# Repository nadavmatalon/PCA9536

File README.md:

# PCA9536 DRIVER

&nbsp;&nbsp;&nbsp;&nbsp;&nbsp;&nbsp;&nbsp;&nbsp;&nbsp;&nbsp;

&nbsp;&nbsp;&nbsp;&nbsp;&nbsp;&nbsp;&nbsp;&nbsp;&nbsp;&nbsp;

&nbsp;&nbsp;&nbsp;&nbsp;&nbsp;&nbsp;&nbsp;&nbsp;&nbsp;&nbsp;

## INTRODUCTION

The PCA9536 is a 4-Channel GPIO Expander with a hardware I2C interface.

The device's 4 channels (i.e. I/O pins) may be controlled all at the same time or individually in terms of their:  
\[1\] Mode (INPUT / OUTPUT), \[2\] State (for output pin mode only: HIGH / LOW), and \[3\] Polarity (for input pin mode only: NON-INVERTED INPUT / INVERTED INPUT). The State (LOW / HIGH) of pins in input mode may be read, whereas thoat of pins in output mode may be either read or written to.

This library contains a complete driver for the PCA9536 exposing all the above functionality, as well as allowing uses to toggle the state of pins in input mode, and the option to recieve verbose information re the device's current settings and/or I2C communication results.

Source: [PCA9536 DATASHEET](http://www.nxp.com/documents/data_sheet/PCA9536.pdf)

## REPOSITORY CONTENTS

- **PCA9536.h** - Library Header file.
- **PCA9536.cpp** - Library Compilation.
- **/utility** 
  - **PCA9536InfoStr.h** - Header file containing a functional extention of the library to include generating pritable information String (see Note #5 below).
  - **PCA9536ComStr.h** - Header file containing a functional extention of the library to include generating a pritable I2C Communication Result String (see Note #6 below).
  - **PCA9536_PString.h** - Header file for PString class (lighter alternative to String class) 
  - **PCA9536_PString.cpp** - Compilation file for PString class (lighter alternative to String class) 
- **/examples**  
  - **/PCA9536_Test**
    - **PCA9536_Test.ino** - A basic sketch for testing whether the PCA9536 is hooked-up and operating correctly.
  - **/PCA9536_Usage**
    - **PCA9536_Usage.ino** - A much more extensive sketch offering a complete usage illustration, as well as a rubust testing mechanism.
  - **/PCA9536_Info**
    - **PCA9536_Info.ino** - A short sketch showing how to generate a Printable Device Information String of the PCA9536's current settings (i.e. Configuration, Limit &anp; Hysteresis registers, etc.).
  - **/PCA9536_I2C_Status**
    - **PCA9536_I2C_Status.ino** - A short sketch for verifying I2C communication has been established between the controller and the PCA9536.
- **/extras** 
  - **License.txt** - A cope of the end-user license agreement.  
  - **/eagle**
    - **PCA9536.sch** - Schematic file for the PCA9536 breakout board.
    - **PCA9536.brd** - Board layout file for the PCA9536 breakout board.
  - **/images**
    - **pca9536_pinout.png** - Pinout image of the PCA9536.
- **keywords.txt** - Keywords for this library which will be highlighted in sketches within the Arduino IDE. 
- **library.properties** - General library properties for the Arduino's IDE (>1.5) Library Package Manager.
- **README.md** - The readme file for this library.
- **library.json** - JSON file for the Arduino's IDE (>1.5) Package Manager.

## HOOK-UP

PIN 1 (IO0) - connect to device requiring digital I/O pin (or leave unconnected)  
PIN 2 (IO1) - connect to device requiring digital I/O pin (or leave unconnected)  
PIN 3 (IO2) - connect to device requiring digital I/O pin (or leave unconnected)  
PIN 4 (GND) - Connect to Arduino GND  
PIN 5 (IO3) - connect to device requiring digital I/O pin (or leave unconnected)  
PIN 6 (SCL) - Connect to Arduino Pin A5 with a 2K2 (400MHz) or 10K (100MHz) pull-up resistor  
PIN 7 (SDA) - Connect to Arduino Pin A4 with a 2K2 (400MHz) or 10K (100MHz) pull-up resistor  
PIN 8 (VCC) - Connect to Arduino 5V output  
DECOUPING   - Connect a 0.1uF Ceramic Capacitor between the PCA9536's VCC & GND pins  

## GENERAL NOTES

1) __I2C Communications Library Dependency__

This library depends on the Arduino IDE's native '[Wire](https://github.com/arduino/Arduino/tree/master/hardware/arduino/avr/libraries/Wire)' library for I2C communication between the Arduino (Master) and the PCA9536 (Slave). 

2) __INPUT &amp; OUTPUT REGISTER VALUES__

It is important to note that the PCA9536 uses an inverse value scheme for designating INPUT and OUTPUT modes than that of the Arduino. In the Arduino environment, INPUT is designated by 0 and OUTPUT by 1, whereas the PCA9536 has INPUT as 1 and OUTPUT as 0.

3) __PULL-UP RESISTORS__

All 4 channels of the PCA9536 have weak pull-up resistors attached (~100K). Hence, if a pin is left 'floating' (or unconnected), it will default to a HIGH state.

4) __Constructor &amp; Destructor__

As PCA9536 instances are initialized without parameters (recall that the single I2C address of the device is factory hardwired), the constructor and destructor have a slightly unconventional format in that they do not include the usual parentheses at the end. For concrete illustrations, see the example sketches bundled in this library.

5) __Device Information String__

It is possible to extend the PCA9536 Library to include a function for generating a pritable device information string showing all the relevant details about the devices current settings. As the additional functionality comes at the cost of increased memory footprint, it was implemented as an optional add-on rather than added directly to the core PCA9536 Library. See the [PCA9536_Info](https://github.com/nadavmatalon/PCA9536/blob/master/examples/PCA9536_Info/PCA9536_Info.ino) example sketch for detailed explanation and an actual usage demo.

6) __Device I2C Communications String__

It is also possible to extend the PCA9536 Library to include a function for generating a pritable I2C Communications string showing the result of each I2C transaction in a human-friendly way, something that may be useful, for example, during debugging sessions. As the additional functionality comes at the cost of increased memory footprint, it was implemented as an optional add-on rather than added directly to the core PCA9536 Library. See the [PCA9536_I2C_Status](https://github.com/nadavmatalon/PCA9536/blob/master/examples/PCA9536_I2C_Status/PCA9536_I2C_Status.ino) example sketch for detailed explanation and an actual usage demo.

## I2C ADDRESS

The PCA9536 has a single I2C address (factory hardwired):

| PART NO.  | BIN      | HEX  | DEC | MARKING |
|-----------|----------|------|-----|---------|
| PCA9536D  | 01000001 | 0x41 | 65  | PCA9536 |

## LIBRARY INSTALLATION & SETUP

Begin by installing the library either by using the Arduino IDE's Installation Wizard (Arduino Version >1.5) or simply by directly downloading the library's ZIP folder  from Github, extracting it, and copying the extraxcted folder into your Arduino '/libraries' folder (don't forget to re-start the Arduino IDE after coping the folder so that the new library will show up in the list of installed libraries).

Next, include the library at the top of the sketch as follows:

```
#include "PCA9536.h"
```

At this point you can construct a new PCA9536 instance(s) by using the following command (place at the top of the sketch after the 'include' line):

```
PCA9536 device_name;  // Notice that the constructor doesn't use parenthesis after device_name! (see Note #3 above)
```

>Replace '__device_name__' above with a name of your choice. As the PCA9536 comes with a single hardwired I2C address, initializations of the class instance is done automatically to that address.

Next, make sure to inlude an instruction for initializing the I2C Bus for the [Wire Library](https://github.com/arduino/Arduino/tree/master/hardware/arduino/avr/libraries/Wire), as follows:

(There's no need to include the Wire Library at the top of the sketch as it's already included by the PCA9536 Library)

```
void setup() {
    Wire.begin();
    // ...other setup code...
}
```

## LIBRARY FUNCTIONS

With the library installed & included in the sketch, and an PCA9536 instance created, the following functions are available (see the usage example sketch for a detailed implementation):

__Note About Methods' Return Values:__  
All 'get' methods return some sort of value (e.g. temp reading, hysteresis setting, etc.), while all 'set' methods return nothing. Nevertheless, ALL methods implicitly update the library's __I2C _comBuffer__ (=communication buffer) after each I2C transmission. The reason for this functional design is to maintain structural coherance between the 'get' and 'set' methods. As 'get' methods cannot return both the desired value and the I2C transmission's result simultaniously. Consequently, if the relevant value hasn't been obtained by a particular 'get' method, the user can simply check the content of the _comBuffer to see what error occured. Similarly, it is possible to check if a particular setting has been successfully applied via a 'set' method either by preforming the corresponding 'get' method - e.g. getHystC() after using setHystC() - or by checking the content of the _comBuffer (0 indicates a successful transmission, 1-6 indicate an error as listed below). 

__ping();__                                  
Parameters:&nbsp;&nbsp;&nbsp;None  
Description:&nbsp;&nbsp;&nbsp;Searches for the PCA9536 at the pre-defined I2C Bus address &amp; returns byte with the relevant success/error code, as follows:  
0  ... Success (no error)  
1  ... Buffer overflow  
2  ... Address sent, NACK received  
3  ... Data send, NACK received  
4  ... Other error (lost bus arbitration, bus error, etc.)  
5  ... Timed-out while trying to become Bus Master  
6  ... Timed-out while waiting for data to be sent  
\>6 ... Unlisted error (potential future implementation/s)<br>

Returns:&nbsp;&nbsp;&nbsp;&nbsp;&nbsp;&nbsp;&nbsp;&nbsp;&nbsp;byte  

__getMode();__  
Parameters:&nbsp;&nbsp;&nbsp;IO0 / IO1 / IO2 / IO3  
Description:&nbsp;&nbsp;Gets the selected pin's current mode (1 = INPUT [default]/ 0 = OUTPUT) (For more info, see General Note #1 above).  
Returns:&nbsp;&nbsp;&nbsp;&nbsp;&nbsp;&nbsp;&nbsp;&nbsp;byte  

__getState();__  
Parameters:&nbsp;&nbsp;&nbsp;IO0 / IO1 / IO2 / IO3  
Description:&nbsp;&nbsp;Gets the selected pin's current state (0 = LOW / 1 = HIGH [default]).  
Returns:&nbsp;&nbsp;&nbsp;&nbsp;&nbsp;&nbsp;&nbsp;&nbsp;byte  

__getPolarity();__  
Parameters:&nbsp;&nbsp;&nbsp;IO0 / IO1 / IO2 / IO3  
Description:&nbsp;&nbsp;Gets the selected INPUT pin's current polarity (0 = NON-INVERTED [default] / 1 = INVERTED). Note that this is relevant only for INPUT pins. The polarity setting determinwes whether reading an INPUT pin returns its actual state or an inverted state.  
Returns:&nbsp;&nbsp;&nbsp;&nbsp;&nbsp;&nbsp;&nbsp;&nbsp;byte  

__setMode();__  
Parameters:&nbsp;&nbsp;&nbsp;To set a single pin: IO0 / IO1 / IO2 / IO3, IO_INPUT [default] / IO_OUTPUT | To set all pins at once: IO_INPUT [default] / IO_OUTPUT  
Description:&nbsp;&nbsp;Sets the selected pin/s mode (INPUT / OUTPUT).  
Returns:&nbsp;&nbsp;&nbsp;&nbsp;&nbsp;&nbsp;&nbsp;&nbsp;None

__setState();__  
Parameters:&nbsp;&nbsp;&nbsp;To set a single OUTPUT pin: IO0 / IO1 / IO2 / IO3, IO_LOW / IO_HIGH [default] | To set all OUTPUT pins at once: IO_LOW / IO_HIGH [default]
Description:&nbsp;&nbsp;Sets the selected pin/s state (LOW / HIGH). Note that this is relevant only for OUTPUT pins.   
Returns:&nbsp;&nbsp;&nbsp;&nbsp;&nbsp;&nbsp;&nbsp;&nbsp;None

__toggleState();__  
Parameters:&nbsp;&nbsp;&nbsp;To toggle the state of a single OUTPUT pin: IO0 / IO1 / IO2 / IO3 | To toggle all OUTPUT pins at once: None
Description:&nbsp;&nbsp;Toggles the selected pin/s state (LOW / HIGH). Note that this is relevant only for OUTPUT pins.   
Returns:&nbsp;&nbsp;&nbsp;&nbsp;&nbsp;&nbsp;&nbsp;&nbsp;None

__setPolarity();__  
Parameters:&nbsp;&nbsp;&nbsp;To set a single INPUT pin: IO0 / IO1 / IO2 / IO3, IO_NON_INVERTED [default] / IO_INVERTED | To set all INPUT pins at once: IO_NON_INVERTED [default] / IO_INVERTED  
Description:&nbsp;&nbsp;Sets the selected pin/s polarity (NON-INVERTED / INVERTED). Note that this is relevant only for INPUT pins.  
Returns:&nbsp;&nbsp;&nbsp;&nbsp;&nbsp;&nbsp;&nbsp;&nbsp;None  

__reset();__  
Parameters:&nbsp;&nbsp;&nbsp;None  
Description:&nbsp;&nbsp;&nbsp;Resets all 4 channels of the PCA9536 to their power-up default settings, as follows:  

* MODE: INPUT
* STATE: HIGH
* POLARITY: NON-INVERTED
* REGISTRY POINTER: INPUT

Returns:&nbsp;&nbsp;&nbsp;&nbsp;&nbsp;&nbsp;&nbsp;&nbsp;&nbsp;None  

__getComResult();__  
Parameters:&nbsp;&nbsp;&nbsp;None  
Description:&nbsp;&nbsp;Returns the latest I2C Communication result code (see Success/Error codes above)  
Returns:&nbsp;&nbsp;&nbsp;&nbsp;&nbsp;&nbsp;&nbsp;&nbsp;byte  

__Destructor__  
If you want to destruct an instantiated PCA9536 object, you can use the following method to do so:  

```
~PCA9536 device_name;      // Notice that the deconstructor doesn't use parenthesis after device_name! (see Note #3 above)
```
>__NOTE__: replace the '__device_name__' above with the name of your PCA9536 device.

## Extended Functionality*

(* requires an additional '\#include' of the relevant *.h file as shown in the corresponding example sketches)

__PCA9536ComStr();__  
Parameters:&nbsp;&nbsp;&nbsp;Name of an initialized PCA9536 instance  
Description:&nbsp;&nbsp;Returns printable string containing human-friendly information about the device's latest I2C communication result  
Returns:&nbsp;&nbsp;&nbsp;&nbsp;&nbsp;&nbsp;&nbsp;&nbsp;PString

__PCA9536InfoStr();__  
Parameters:&nbsp;&nbsp;&nbsp;Name of an initialized PCA9536 instance  
Description:&nbsp;&nbsp;Returns printable string containing detailed information about the device's current settings   
Returns:&nbsp;&nbsp;&nbsp;&nbsp;&nbsp;&nbsp;&nbsp;&nbsp;PString

## RUNNING THE EXAMPLE SKETCHES

1) Start the Arduino IDE and open the relevant example sketch  
2) Hook-up the PCA9536 to the Arduino as explained in the sketch's notes  
3) Upload the sketch to the Arduino  
4) Open the Serial Communications Window (make sure the baud-rate is set to 9600 or change it in the sketch to match your Serial Port's buad-rate)  

## BUG REPORTS

Please report any issues/bugs/suggestions at the [Issues](https://github.com/nadavmatalon/PCA9536/issues) section of this Github repository.

## TODO

## VERSION HISTORY

__Ver. 1.0.0__ - First release (24.10.16)  

## LICENSE

[The MIT License (MIT)](https://opensource.org/licenses/MIT)
Copyright (c) 2016 Nadav Matalon

Permission is hereby granted, free of charge, to any person obtaining a copy of this software and associated documentation files (the "Software"), to deal in the Software without restriction, including without limitation the rights to use, copy, modify, merge, publish, distribute, sublicense, and/or sell copies of the Software, and to permit persons to whom the Software is furnished to do so, subject to the following conditions:

The above copyright notice and this permission notice shall be included in all copies or substantial portions of the Software.

THE SOFTWARE IS PROVIDED "AS IS", WITHOUT WARRANTY OF ANY KIND, EXPRESS OR IMPLIED, INCLUDING BUT NOT LIMITED TO THE WARRANTIES OF MERCHANTABILITY, FITNESS FOR A PARTICULAR PURPOSE AND NONINFRINGEMENT. IN NO EVENT SHALL THE AUTHORS OR COPYRIGHT HOLDERS BE LIABLE FOR ANY CLAIM, DAMAGES OR OTHER LIABILITY, WHETHER IN AN ACTION OF CONTRACT, TORT OR OTHERWISE, ARISING FROM, OUT OF OR IN CONNECTION WITH THE SOFTWARE OR THE USE OR OTHER DEALINGS IN THE SOFTWARE.

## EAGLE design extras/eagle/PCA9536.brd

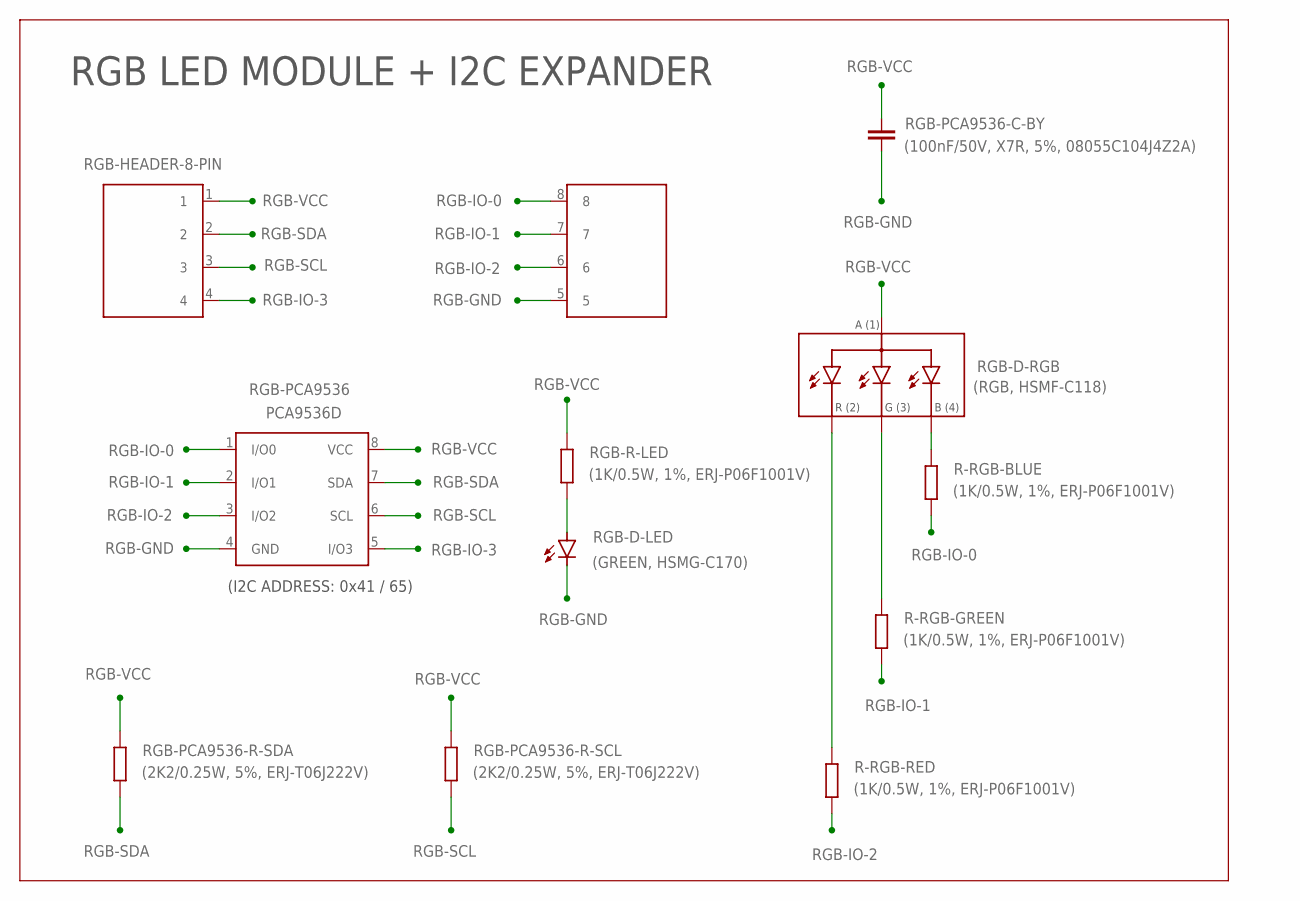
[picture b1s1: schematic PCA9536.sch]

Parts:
R-RGB-BLUE: (1K/0.5W, 1%, ERJ-P06F1001V); 0805
R-RGB-GREEN: (1K/0.5W, 1%, ERJ-P06F1001V); 0805
R-RGB-RED: (1K/0.5W, 1%, ERJ-P06F1001V); 0805
RGB-D-LED: (GREEN, HSMG-C170); DIODE_0805
RGB-D-RGB: (RGB, HSMF-C118); DIODE_LED_1210_RGB
RGB-J1: RGB-HEADER-8-PIN; HEADER_2.54MM_8_PIN_VER
RGB-PCA9536: PCA9536D; SOIC-8-NARROW
RGB-PCA9536-C-BY: (100nF/50V, X7R, 5%, 08055C104J4Z2A); 0805
RGB-PCA9536-R-SCL, RGB-PCA9536-R-SDA: (2K2/0.25W, 5%, ERJ-T06J222V); 0805
RGB-R-LED: (1K/0.5W, 1%, ERJ-P06F1001V); 0805

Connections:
RGB-GND: RGB-D-LED.C, RGB-J1.5, RGB-PCA9536.4 (GND), RGB-PCA9536-C-BY.1 (A)
RGB-IO-0: R-RGB-BLUE.1, RGB-J1.8, RGB-PCA9536.1 (I/O0)
RGB-IO-1: R-RGB-GREEN.1, RGB-J1.7, RGB-PCA9536.2 (I/O1)
RGB-IO-2: R-RGB-RED.1, RGB-J1.6, RGB-PCA9536.3 (I/O2)
RGB-IO-3: RGB-J1.4, RGB-PCA9536.5 (I/O3)
RGB-POWER: RGB-D-LED.A, RGB-R-LED.1
RGB-R-BLUE: R-RGB-BLUE.2, RGB-D-RGB.4
RGB-R-GREEN: R-RGB-GREEN.2, RGB-D-RGB.3
RGB-R-RED: R-RGB-RED.2, RGB-D-RGB.2
RGB-SCL: RGB-J1.3, RGB-PCA9536.6 (SCL), RGB-PCA9536-R-SCL.1
RGB-SDA: RGB-J1.2, RGB-PCA9536.7 (SDA), RGB-PCA9536-R-SDA.1
RGB-VCC: RGB-D-RGB.1, RGB-J1.1, RGB-PCA9536.8 (VCC), RGB-PCA9536-C-BY.2 (C), RGB-PCA9536-R-SCL.2, RGB-PCA9536-R-SDA.2, RGB-R-LED.2

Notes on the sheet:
RGB LED MODULE + I2C EXPANDER
(I2C ADDRESS: 0x41 / 65)

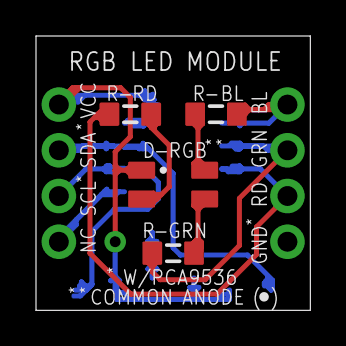
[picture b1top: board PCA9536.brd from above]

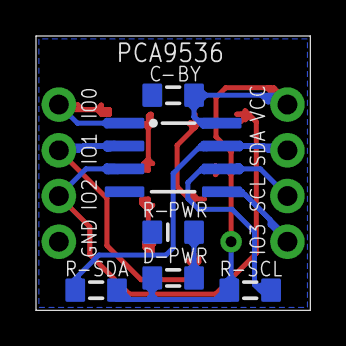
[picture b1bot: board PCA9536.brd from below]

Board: 2 copper layers, 15.2 x 15.2 mm, 11 parts (6 on the bottom side), 12 nets.

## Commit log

2016-10-24 added .gitattributes file
2016-10-25 added toggleState function
2016-10-25 cosmetic fixes
2016-10-25 fixed setPin function
2016-10-26 updated setPolarity function and completed full usage exaple
2016-10-26 added eagle breakout board design
2016-10-26 added comStr and infoStr functionality
2016-10-26 added test device example sketch
2016-10-26 added I2C Status string example sketch
2016-10-26 added code & example for device info string friend function
2016-10-26 updated documentation
2016-10-26 updated initializer
2016-10-28 update documentation
2016-12-06 added pinout image
2020-03-08 Update PCA9536.h
    These lines cause this code to error for non-avr architectures, like arm. Since this is an Arduino library, I think its safe to assume the Wire library will exist for any arduino architecture, since 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
    #if !defined(ARDUINO_ARCH_AVR)
    #error “The PCA9536 library only supports AVR processors.”
    #endif
2024-02-07 Update PCA9536.h
    Removed AVR only restriction as not needed (library works on ESP32 as well).
2024-02-07 Update library.properties
    bumped minor version
